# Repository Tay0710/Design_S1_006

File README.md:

# ELEC5550 Group Project (Team 0-06)

**Students Involved:**
- Aidan	Wheller
- Dorothy	Jong
- Emersyn Johnson
- Owen Spicer
- Samuel Dixon
- Taylah Karran

## 🚀 Project Summary

This project integrates hardware, firmware, and design elements to develop a fully functional autonomous 3D mapping drone system. This iteration of the design involves a drone capable of autonomously navigating the operation environment of Lv4 EECE, a LoRa-based kill switch which covers the entire operation environment, a mapping test rig used to manually collect data from 2 independent mapping systems, and a 3D mapping python pipeline which runs on the base station, used to convert raw mapping data from the test rig into 2 independent maps plus a combined map.

The next iteration of this design aims to combine the mapping test rig with the autonomous drone platform, creating a fully integrated autonomous 3D mapping drone system which follows the system architecture diagram below.

.png)

## 📁 Folder Structure

```
📁 Root Directory

├── 📂 3D Mapping
│   └── 3D mapping
│   └── optical_flow_method
│   └── optical_flow_method_data
│
├── 📂 CAD Design
│   └── 3D-printed Parts
│   └── Full_Model
│   └── LoRa Kill Switch
│
├── 📂 Drone Firmware
│   └── Flight Computer Firmware
│   └── Flight Controller Firmware
│
├── 📂 LoRa Drone Receiver Test Firmware
│   └── LORA_DRONE_RECEIVER
│
├── 📂 LoRa Kill Switch Firmware
│   └── LORA_TRANSMITTER_BUTTON
│
├── 📂 PCB Design
│   └── ESP32_BOARD_V2
│   └── STM32_BOARD_V3
│
├── 📂 Test Rig Firmware
│   └── Test Rig Data Collection
│   └── Test Rig FreeRTOS
│
└── 📂 Videos
```

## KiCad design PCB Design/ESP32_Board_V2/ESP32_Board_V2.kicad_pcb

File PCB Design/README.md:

# ELEC5550 Group Project (Team 0-06)

**Students Involved:**
- Aidan	Wheller
- Dorothy Jong
- Emersyn Johnson
- Owen Spicer
- Samuel Dixon
- Taylah Karran

## 📁 Project Overview - PCB Design

**Folder Summary:**

This folder contains all PCB schematics, design files, and related documentation required for manufacturing the printed circuit board (PCB) for the ESP32 flight computer and STM32 flight controller. It includes the necessary Gerber files, bill of materials (BOM), and design source files to ensure accurate production and assembly. All PCB projects can be viewed through KiCAD, which can be downloaded through this [link](https://www.kicad.org/download/).

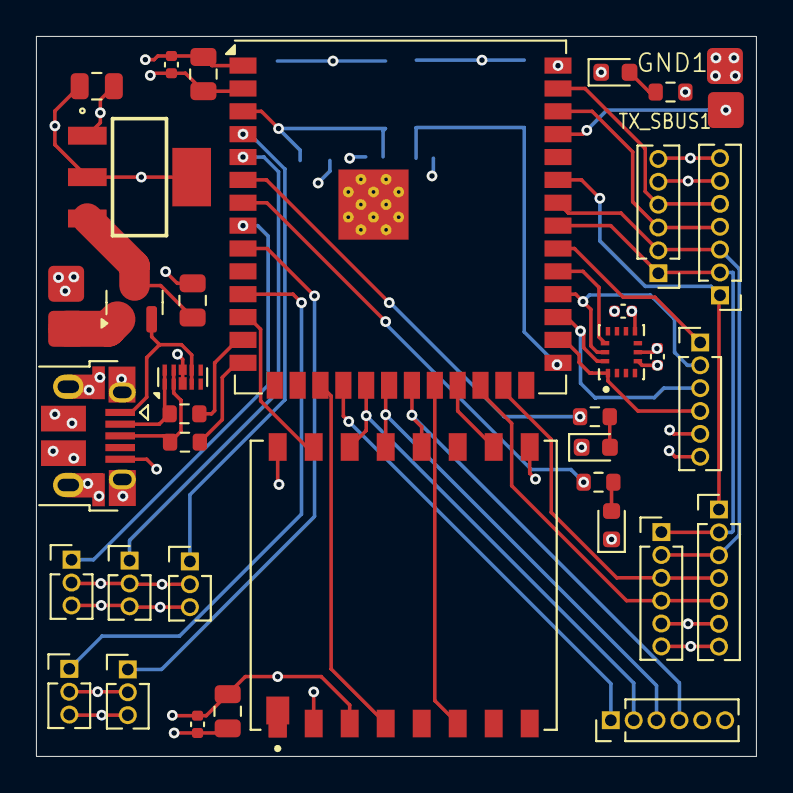
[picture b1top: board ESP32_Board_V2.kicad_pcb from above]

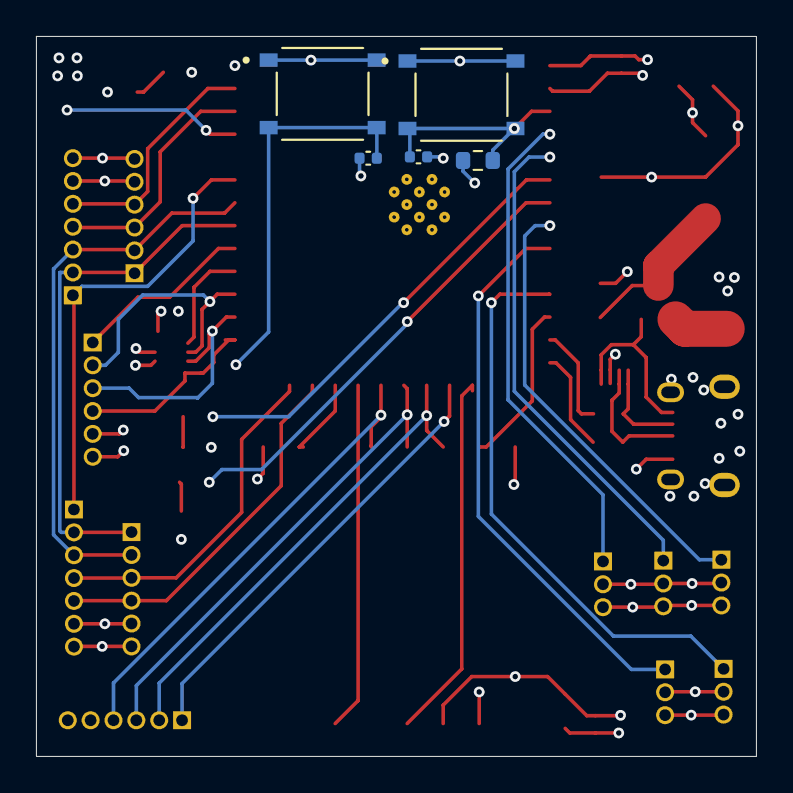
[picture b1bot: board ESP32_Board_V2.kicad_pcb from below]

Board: 4 copper layers, 40.0 x 40.0 mm, 42 parts (5 on the bottom side), 42 nets.

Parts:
C1, C15: 10u/10V; C_0805_2012Metric
C2: 100n/10V; C_0402_1005Metric
C9, C12, C13, C14, C23: 0.1u/10V; C_0402_1005Metric
C17, C19: 10u/16V; C_0805_2012Metric
D1, D4, D5: LED; LED_0603_1608Metric
D6: BAT54C; SOT-23
ESP3V3: NCP1117ST33T3G; SOT230P700X180-4N
GND1: GND; SolderPad_2mm
J6: USB_B_Micro; USB_Micro-B_Amphenol_10103594-0001LF_Horizontal
J7: US1; PinHeader_1x03_P1.27mm_Vertical
J8: US2; PinHeader_1x03_P1.27mm_Vertical
J9: US3; PinHeader_1x03_P1.27mm_Vertical
J10: US4; PinHeader_1x03_P1.27mm_Vertical
J11: US5; PinHeader_1x03_P1.27mm_Vertical
J12: TOF1; PinHeader_1x06_P1.27mm_Vertical
J13: TOF2; PinHeader_1x07_P1.27mm_Vertical
J14: TOF3; PinHeader_1x06_P1.27mm_Vertical
J15: TOF4; PinHeader_1x07_P1.27mm_Vertical
J16: SD Card; PinHeader_1x06_P1.27mm_Vertical
J17: Optical Flow; PinHeader_1x06_P1.27mm_Vertical
J20: BATTERYESP; 2_SolderPad_2mm
R1, R8, R9: 1k; R_0603_1608Metric
R10, R11: 22; R_0603_1608Metric
R12: 10k; R_0603_1608Metric
S1, S2: TS-1187A-B-A-B; SW_TS-1187A-B-A-B
TX_SBUS1: TX_SBUS; SolderPad_2mm
U1: ESP32-S3-WROOM-1; ESP32-S3-WROOM-1U
U2: RA-01H; XCVR_RA-01H
U5: D3V3XA4B10LP; Diodes_UDFN-10_1.0x2.5mm_P0.5mm
U7: ICM-45686; IC_ICM-45686

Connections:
/ESP32/3V3: C1.1, C2.1, C9.2, C14.1, C15.1, C17.1, C23.2, ESP3V3.2 (OUT), ESP3V3.4 (OUT), J7.2, J8.2, J9.2, J10.2, J11.2, J12.5, J13.6, J14.5, J15.6, J16.5, J17.5, R1.2, R12.1, U1.2 (3V3), U2.3 (3.3V), U7.5 (VDDIO), U7.8 (VDD)
/ESP32/5V_USB2: D6.2, J6.1 (VBUS), U5.4, U5.7 (NC)
/ESP32/AP_CS2: U1.31 (IO38), U7.12 (AP_CS)
/ESP32/AP_SCLK2: J17.2, U1.30 (IO37), U7.13 (AP_SCL/AP_SCLK)
/ESP32/AP_SDI2: J17.3, U1.29 (IO36), U7.14 (AP_SDA/AP_SDIO/AP_SDI)
/ESP32/AP_SDO2: J17.4, U1.28 (IO35), U7.1 (AP_SDO/AP_AD0)
/ESP32/BOOT: C13.1, S2.C, S2.D, U1.27 (IO0)
/ESP32/CLK1: J16.4, U1.21 (IO13), U2.12 (SCK)
/ESP32/CSLORA: U1.12 (IO8), U2.15 (NSS)
/ESP32/CSOF: J17.1, U1.32 (IO39)
/ESP32/CSSD: J16.1, U1.18 (IO10)
/ESP32/ENABLE: C12.1, R12.2, S1.C, S1.D, U1.3 (EN)
/ESP32/LED3: R8.2, U1.6 (IO6)
/ESP32/LED4: R9.2, U1.7 (IO7)
/ESP32/LORA_BUSY: U1.23 (IO21), U2.10 (BUSY)
/ESP32/LORA_DIO: U1.22 (IO14), U2.6 (DIO1)
/ESP32/LORA_RESET: U1.17 (IO9), U2.4 (RESET)
/ESP32/LPN: J13.1, J15.1, U1.35 (IO42)
/ESP32/MISO1: J16.3, U1.20 (IO12), U2.13 (MISO)
/ESP32/MOSI1: J16.2, U1.19 (IO11), U2.14 (MOSI)
/ESP32/PENA: J12.1, J13.2, J14.1, J15.2, U1.33 (IO40)
/ESP32/RESET: J12.2, J13.3, J14.2, J15.3, U1.34 (IO41)
/ESP32/SCL1: J12.4, J13.5, U1.24 (IO47)
/ESP32/SCL2: J14.4, J15.5, U1.39 (IO1)
/ESP32/SDA1: J12.3, J13.4, U1.25 (IO48)
/ESP32/SDA2: J14.3, J15.4, U1.38 (IO2)
/ESP32/TX0: TX_SBUS1.1, U1.37 (TXD0)
/ESP32/US1: J7.1, U1.11 (IO18)
/ESP32/US2: J8.1, U1.8 (IO15)
/ESP32/US3: J9.1, U1.9 (IO16)
/ESP32/US4: J10.1, U1.4 (IO4)
/ESP32/US5: J11.1, U1.5 (IO5)
/ESP32/USB_N: J6.2 (D-), R10.2, U5.1, U5.10 (NC)
/ESP32/USB_P: J6.3 (D+), R11.2, U5.2, U5.9 (NC)
GND: C1.2, C2.2, C9.1, C12.2, C13.2, C14.2, C15.2, C17.2, C19.2, C23.1, D1.1 (K), D4.1 (K), D5.1 (K), ESP3V3.1 (GND), GND1.1, J6.5 (GND), J6.6 (Shield), J7.3, J8.3, J9.3, J10.3, J11.3, J12.6, J13.7, J14.6, J15.7, J16.6, J17.6, J20.2, S1.A, S1.B, S2.A, S2.B, U1.1 (GND), U1.40 (GND), U1.41 (GND), U2.2 (GND), U2.9 (GND), U2.16 (GND), U5.3 (VSS), U5.8 (VSS), U7.6 (GND)
unnamed: D1.2 (A), R1.1
unnamed: D4.2 (A), R8.1
unnamed: D5.2 (A), R9.1
unnamed: C19.1, D6.3, ESP3V3.3 (IN)
unnamed: D6.1, J20.1
unnamed: R11.1, U1.14 (USB_D+)
unnamed: R10.1, U1.13 (USB_D-)

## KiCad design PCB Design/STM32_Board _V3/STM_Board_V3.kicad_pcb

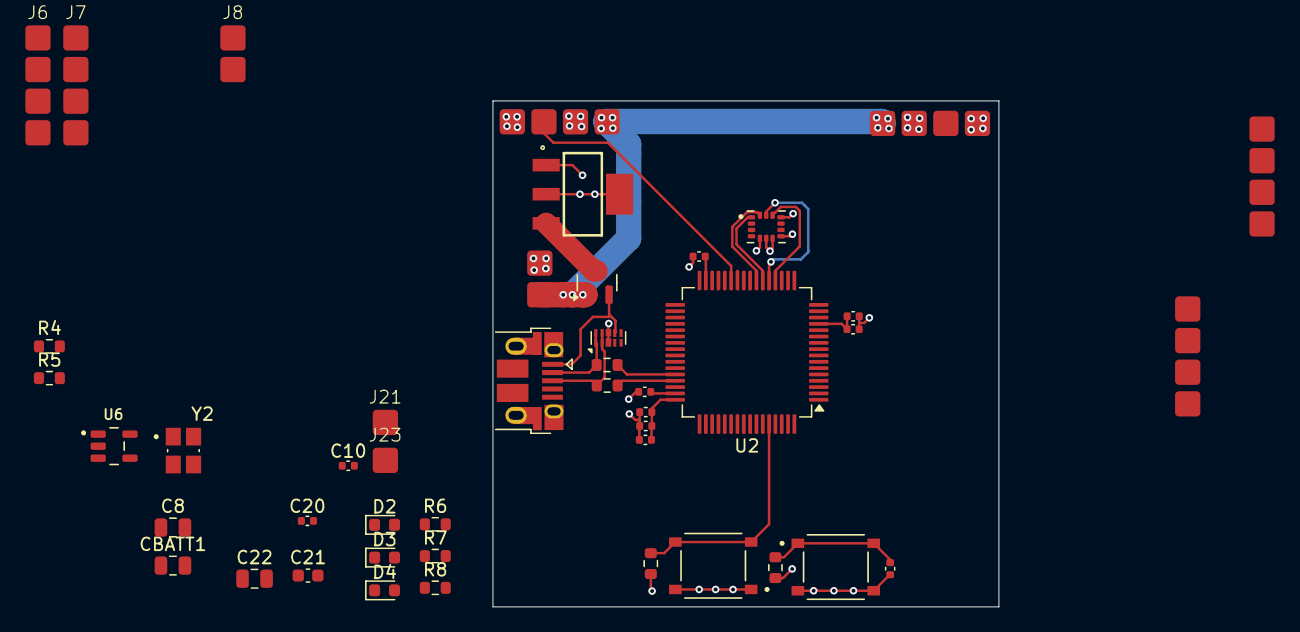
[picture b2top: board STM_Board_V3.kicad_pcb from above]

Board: 4 copper layers, 40.0 x 40.0 mm, 46 parts (0 on the bottom side), 39 nets.

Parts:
C1, C2, C3, C4, C5, C6, C7, C10, C20: C49062; C_0402_1005Metric
C8: C1713; C_0805_2012Metric
C9: 100n; C_0402_1005Metric
C21: C1531; C_0603_1608Metric
C22: C1710; C_0805_2012Metric
CBATT1: C1713; C_0805_2012Metric
D1: C2135; SOT-23
D2, D4: C2286; LED_0603_1608Metric
D3: C2290; LED_0603_1608Metric
J1: C136001; USB_Micro-B_Amphenol_10103594-0001LF_Horizontal
J2: S1; 4_SolderPad_2mm
J3: S2; 4_SolderPad_2mm
J4: S3; 4_SolderPad_2mm
J5: S4; 4_SolderPad_2mm
J6: ST-LINK; 4_SolderPad_2mm
J7: UART-FLASH; 4_SolderPad_2mm
J8: SBUS; 2_SolderPad_2mm
J18: BATTERYSTM; 2_SolderPad_2mm
J21: STM32GROUND; SolderPad_2mm
J23: SBUS_IN; SolderPad_2mm
R1, R4, R5: C15401; R_0603_1608Metric
R2, R3: C1203; R_0603_1608Metric
R6, R7, R8: C14676; R_0603_1608Metric
R9: 10k; R_0603_1608Metric
S1, S2: C318884; SW_TS-1187A-B-A-B
STM3V3: C26537; SOT230P700X180-4N
U1: D3V3XA4B10LP; Diodes_UDFN-10_1.0x2.5mm_P0.5mm
U2: C15742; LQFP-64_10x10mm_P0.5mm
U4: C1850418; PQFN50P300X250X97-14N
U6: C7827; SOT95P280X145-5N
Y2: C5140594; XTAL_ABM8AIG-8.000MHZ-1Z-T

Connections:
/IMU1/3V3: C1.1, C2.1, C3.1, C4.1, C5.1, C8.1, C10.2, C20.2, C21.2, C22.1, J6.3, J7.3, R8.2, R9.2, S2.A, S2.B, STM3V3.2 (OUT), STM3V3.4 (OUT), U2.1 (VBAT), U2.13 (VDDA), U2.19 (VDD), U2.32 (VDD), U2.48 (VDD), U2.64 (VDD), U4.5 (VDDIO), U4.8 (VDD), U6.5
/LEDs/LED1: R6.2, U2.56 (PB4)
/LEDs/LED2: R7.2, U2.57 (PB5)
/STM32/5V_USB1: D1.2, J1.1 (VBUS), R5.1, U1.4, U1.7 (NC)
/STM32/AP_CS: U2.20 (PA4), U4.12 (AP_CS)
/STM32/AP_SCLK: U2.21 (PA5), U4.13 (AP_SCL/AP_SCLK)
/STM32/AP_SDI: U2.23 (PA7), U4.14 (AP_SDA/AP_SDIO/AP_SDI)
/STM32/AP_SDO: U2.22 (PA6), U4.1 (AP_SDO/AP_AD0)
/STM32/BATT: D1.1, J2.1, J3.1, J4.1, J5.1, J18.1
/STM32/BOOT: R1.1, S2.C, S2.D, U2.60 (BOOT0)
/STM32/INT1: U2.24 (PC4), U4.4 (INT1/INT)
/STM32/INT2: U2.28 (PB2), U4.9 (INT2/FSYNC/CLKIN)
/STM32/RESET: C9.2, R9.1, S1.A, S1.B, U2.7 (NRST)
/STM32/RX_4: U2.15 (PA1), U6.4
/STM32/RX_ESP32_IN: J23.1, U6.2
/STM32/RX_SBUS: J8.1, U2.54 (PD2)
/STM32/S1: J2.3, U2.17 (PA3)
/STM32/S2: J3.3, U2.26 (PB0)
/STM32/S3: J4.3, U2.27 (PB1)
/STM32/S4: J5.3, U2.16 (PA2)
/STM32/SWCLK: J6.2, U2.49 (PA14)
/STM32/SWDIO: J6.1, U2.46 (PA13)
/STM32/TX_SBUS: J8.2, U2.53 (PC12)
/STM32/USART1_RX: J7.1, U2.43 (PA10)
/STM32/USART1_TX: J7.2, U2.42 (PA9)
/STM32/USB_N: J1.2 (D-), R3.2, U1.1, U1.10 (NC)
/STM32/USB_P: J1.3 (D+), R2.2, U1.2, U1.9 (NC)
GND: C1.2, C2.2, C3.2, C4.2, C5.2, C6.2, C7.2, C8.2, C9.1, C10.1, C20.1, C21.1, C22.2, CBATT1.2, D2.1 (K), D3.1 (K), D4.1 (K), J1.5 (GND), J1.6 (Shield), J2.2, J2.4, J3.2, J3.4, J4.2, J4.4, J5.2, J5.4, J6.4, J7.4, J18.2, J21.1, R1.2, R4.2, S1.C, S1.D, STM3V3.1 (GND), U1.3 (VSS), U1.8 (VSS), U2.12 (VSSA), U2.18 (VSS), U2.63 (VSS), U4.6 (GND), U4.7 (RESV_7), U4.11 (RESV_11), U6.1, U6.3, Y2.2 (GND), Y2.4 (GND__1)
unnamed: D2.2 (A), R6.1
unnamed: D3.2 (A), R7.1
unnamed: D4.2 (A), R8.1
unnamed: CBATT1.1, D1.3, STM3V3.3 (IN)
unnamed: R3.1, U2.44 (PA11)
unnamed: R2.1, U2.45 (PA12)
unnamed: R4.1, R5.2, U2.25 (PC5)
unnamed: U2.5 (PH0), Y2.3
unnamed: U2.6 (PH1), Y2.1
unnamed: C7.1, U2.31 (VCAP_1)
unnamed: C6.1, U2.47 (VCAP_2)

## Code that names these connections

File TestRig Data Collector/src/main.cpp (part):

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#include <Bitcraze_PMW3901.h>

// Optical flow SPI pins (pins for Owen's ESP32)
#define MOSI1 11 // OF, VSPI
#define CLK1 12
#define MISO1 13
#define CS1 10

#define AP_SDI2 37 // IMU / ICM - PSRAM
#define AP_CLK2 36 // SDO = MISO; SDI = MOSI
#define AP_SDO2 38
#define AP_CS2 35

#define SDCLK 47 // SD Card, HSPI
#define SDMISO 48
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#define SDA2 6
#define SCL2 7
// ToF inputs. 
#define PENA 41 // Power enable
#define RESET 40
#define LPN 42

#define US1 14
#define US2 15
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
// Address Reset sequence for ToFL7 sensors.
// Activating PWR_EN (Make High). 
  pinMode(PENA, OUTPUT);
  digitalWrite(PENA, HIGH); 
  delay(100);   
// Activating I2C Reset pin to reset the addresses (Pulse High). 
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  delay(100);   
  digitalWrite(PENA, HIGH); // Make High again.
  delay(100);  
  // Configure LPn pins
  pinMode(LPN, OUTPUT);
  // Set Sensor 1 LPn low (Deactivate I2C communication). 
  digitalWrite(LPN, LOW); // One LPn should be set HIGH permanently
  delay(100); 

  // I2C Bus split: S1 + R on I2C1; S2 + F on I2C2
  // Have to change the address of the ToFs with no LPN pin attached.
  // Make R & F the changed Address sensors. 


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
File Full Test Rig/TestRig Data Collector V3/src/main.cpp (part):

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#define VSPI_MOSI 36 // OF and IMU, VSPI
#define VSPI_CLK 37
#define VSPI_MISO 35
#define CSOF 39
#define CSIMU 38

#define HSPI_CLK 13 // SD Card, HSPI
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#define SCL1 47  
#define SDA2 2
#define SCL2 4
#define PENA 40 // Power enable
#define RESET 41 // I2C reset
#define LPN 42

#define USD 15 // Downwards-mounted ultrasonic PW pin
// #define USU 4 // Upwards-mounted ultrasonic PW pin
#define USL 18 // Left-mounted ultrasonic PW pin
#define USR 5 // Right-mounted ultrasonic PW pin
#define LED1 6 // PCB LED

#define BOOT_PIN 0

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}

void setup() {
  pinMode(LED1, OUTPUT);
  delay(100);
  digitalWrite(LED1, HIGH);

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  // Initialise 4 ToF sensors
  // Address reset sequence for ToFL7 sensors.
  // Activating PWR_EN (Make High). 
  pinMode(PENA, OUTPUT);
  delay(200); 
  digitalWrite(PENA, HIGH); 
  delay(200);   
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  delay(200);   
  digitalWrite(PENA, HIGH); // Make high again
  delay(200);  
  // Configure LPn pins
  pinMode(LPN, OUTPUT);
  delay(200);
  // Set sensor 1 LPn low (Deactivate I2C communication) 
  digitalWrite(LPN, LOW); // One LPn should be set HIGH permanently
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  Serial.println("Clock Has been Set for I2Cs");

  // I2C bus split: L + U on I2C_bus2; R + D on I2C_bus1
  // Have to change the address of the ToFs with no LPN pin attached.
  // U + D are the sensors that have their address changed

  // Change sensor address to 0x30 after calling begin()
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
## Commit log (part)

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2025-09-18 Added detail to README
2025-09-18 Updated orientation
2025-09-18 Fixed orientation
2025-09-18 Added READMEs
2025-09-18 Created for mapping base.
2025-09-18 added figures for Lshaped data
2025-09-18 Created to transition the test code to a real data point from the ToF.
2025-09-18 Position pipeline ran to update data files.
2025-09-18 Added README
2025-09-18 Changed frequency of OF
2025-09-18 fixed OF y velocity direction
2025-09-18 add figure
2025-09-18 update data
2025-09-18 updated data s2
2025-09-18 Created to transition to all data sets from one sample tof data set in a previous script. Working well.
2025-09-18 added data times
2025-09-18 tuned scale factor for tof and fixed imu truncation
2025-09-19 Updated to include overarching documentation.
2025-09-19 Updated to include mesh.
2025-09-19 Updated to remove the outliers less than 0.2m from the drone. Mesh is not right so it has been commented out.
2025-09-19 Updated documentation.
2025-09-19 Update spacing.
2025-09-19 Created README.
2025-09-19 added more comparisons
2025-09-19 Changed board and made new project
2025-09-19 Added reading for the SQUAL and SHUTTER registers
2025-09-19 Archived old code
2025-09-19 Wrote code to read ultrasonic using interrupts
2025-09-19 updated x4 with differentiated acceleration
2025-09-19 Updated files
2025-09-19 Updated pins
2025-09-19 Changed buffer sizes and variable names
2025-09-19 Changed dps
2025-09-20 sync
2025-09-20 notes
2025-09-20 two US interrupts, w timing
2025-09-20 Added extra time variables
2025-09-20 Changed frequency and comments
2025-09-20 Moved auxiliary functions
2025-09-20 Changed ToF to separate CSVs and renamed pins
2025-09-20 Changed ultrasonic functions such that they now use interupts
2025-09-20 Changed SPI bus initialisation
2025-09-20 Standardised initialisation structure
2025-09-20 Changed ToF sensor names
2025-09-20 Added files for each ToF
2025-09-20 Added extra files to closing process
2025-09-20 Fixed i2c issue for sensor U
2025-09-21 updating
2025-09-21 Fixed i2c bus issues
2025-09-21 Removed alternate code
2025-09-21 Merged ToF data into one file such that the max number of files open is not exceeded
2025-09-21 Chaning the order of logic for ToF data collection.
2025-09-21 Removed unnecessary int
2025-09-21 Changed ToF to common timestamp
2025-09-21 Changed ultrasonic pin, fixing ultrasonic data collection
2025-09-21 Added frequency specification to increase polling speed
2025-09-21 Moved ToF timer check out of individual ToF function
2025-09-21 Removed delay printing
2025-09-21 Swapped pins of sensors L and R
2025-09-22 Fixed ToF indexing issue
2025-09-22 Minor formatting
2025-09-22 New sample with full test rig
2025-09-22 Added two new samples
2025-09-22 Added samples
2025-09-22 New sample
2025-09-22 Added sample 7
2025-09-22 Updated to match the new tof file format with type column.
2025-09-22 From pipeline run.
2025-09-22 Updated to include functions for the up and down tof.
2025-09-22 Saved images for tof mapping progress.
2025-09-22 Created video for full map of 1_rectangle.
2025-09-22 Updated to include the 8x8 tofs on the left and right.
2025-09-22 Updated to run various data sets.
2025-09-23 Updated times on README
2025-09-23 work in progress: updating z positioning
2025-09-23 include z position in csv
2025-09-23 added 7_lyco_lab data set
2025-09-23 rtos code
2025-09-23 1_L_cards sample added
2025-09-23 2 samples added
2025-09-23 updated screen and button
2025-09-23 Addition of MUTEX for SD card write
2025-09-23 Fixing Debounce Button
2025-09-23 added acceleration in world frame
2025-09-23 added new imu experiments
2025-09-24 Updated for new sample.
2025-09-24 Updated to incorporate the rotation matrix in the ToF distance calculation.
2025-09-24 Update comments.
2025-09-24 Fixing ToF racing condition and Stack smashing protect failure (increase Char size)
2025-09-24 correcting tof task core
2025-09-24 Added read of z_pos_body array
2025-09-24 Currently Crashes out after 53seconds of CSV recording.
2025-09-24 Generalised rotate_to_world function
2025-09-24 Added function to rotate z position to world
2025-09-24 Added function to generate rotated z position then added
2025-09-24 Changed code to add the z position witin the function. Renamed function to add_z_position
2025-09-24 Removed call of rotate world function in the add_z_position code
2025-09-25 update button to match pcb
2025-09-26 Added threshold to z_position_calc function
2025-09-26 Added pillar 2 sample
2025-09-26 Moved folders and added wrapping paper
2025-09-26 update things
2025-09-26 Addition of Ultrasonic Detection
2025-09-26 Implemented Hover code with Ultrasonic
2025-09-26 Implementing nonblocking throttle delays
2025-09-27 Fixed sensor axis orientation, fov and negated y-axis ToF angles
2025-09-27 Removed the need for the cell_angles arrays
2025-09-27 add changes to test file
2025-09-27 update requirements
2025-09-27 added new version with new maths
2025-09-27 added a statistical outlier filter
2025-09-29 adding pid lib
    adding pid lib
2025-09-29 adding pid code.
2025-09-29 udpatessss
2025-09-29 PID tuning
2025-09-29 added colours for each sensor
2025-10-01 Added data collector V3 code
2025-10-01 adding prints + create sdcard module test file
2025-10-01 included speed write test
2025-10-01 I agree it does not work.
2025-10-01 Added offsets to the point cloud generation
2025-10-02 Added lv4 sticker samples
2025-10-02 add debounce to dpad, add higher throttle value to arm sequence
2025-10-02 added new folder
2025-10-02 fixed some pid stuff
2025-10-03 changed throttle values
2025-10-03 Update pipeline and optical flow folder to remove references to stages 7/8.
2025-10-04 added sync words for private LoRa networks
2025-10-05 drone hover testing
2025-10-05 returns a point distance.
2025-10-05 pitch adjustments testing
2025-10-06 pitch code improvement
2025-10-06 not sure
2025-10-06 Update current tof map name.
2025-10-06 Updated to remove the main call of deleted stages 7/8.
2025-10-06 Created ultrasonic map based off of the tof code. Included capacity to crop the ultrasonic data.
2025-10-06 Updated to link to the mapping pipeline.
2025-10-06 Updated to remove the crop code as this functionality has been moved to the mapping pipeline file.
2025-10-06 Updated to remove double-up of numpy import.
2025-10-06 Moved file to the archive folder.
2025-10-06 Created file through the mapping pipeline.
2025-10-06 Updated to include new mapping pipeline.
2025-10-06 Moved unnecessary mapping files to archive.
2025-10-06 Updated to include how to run the position and mapping pipelines.
2025-10-06 Updated to remove the oython 11 version note.
2025-10-06 Updated to include to save the tof and us point clouds and combine them.
2025-10-06 Added final flight controller firmware
    Upload using STMCubeProgrammer
2025-10-07 addaition of front US code. and arm sequence changes.
2025-10-07 addition of ToF
    increasing pitch due to extra weight, as well as throttle. Testing YAW with TOF works nicely.
2025-10-07 notes added
2025-10-08 Reorganise previous method filesl
2025-10-08 Updated to include corner extrapolation.
2025-10-08 Created a new version for the introduction of wall extrapolation.
2025-10-08 Updated to include additional extrapolation.
2025-10-09 Removed loop activity pin
2025-10-09 Pins changed for testing
2025-10-09 Changed to S3 board
2025-10-10 logic fixes with drone turning Left
2025-10-10 syntax fixes.
2025-10-10 fixed settings for single wire antenna
2025-10-10 Changed pins
2025-10-10 Changed board to S3
2025-10-10 Added custom i2c pins
2025-10-10 Changed to ESP32 S3
2025-10-10 Changed pin numbers to match PCB
2025-10-10 Updated pins to match new PCB
2025-10-10 Update bins and bus type
2025-10-10 New project added for simple IMU data collection
2025-10-10 Renamed project
2025-10-10 Made new code for sampling two ToFs on one I2C bus
2025-10-14 Updates file names.
2025-10-14 Added fake ultrasonic data to lyco sample
2025-10-15 Update to call new extrapolated ultrasonic code through the pipeline.
2025-10-15 Updated the filepath.
2025-10-15 Updated to include fusion attempt.
2025-10-15 Updated to include combination map.
2025-10-15 Created to create individual tof and ultrasonic maps, as well as a combination map with filtering.
2025-10-16 udpate
2025-10-16 Roll works
2025-10-18 Changed US pins
2025-10-20 Updated to include new colours.
2025-10-21 Moving LED blink
2025-10-22 Added test rig V4
2025-10-22 Updated the requirements file.
2025-10-22 Updated to include all maps.
2025-10-22 Created to display various forms of filtering in the XY axes on the fused map.
2025-10-22 new samples
2025-10-22 Comparison of map filtering images.
2025-10-22 Updated to remove extrapolated ultrasonic data.
2025-10-22 fixed lora for drone pcb
2025-10-22 New files based on updated data.
2025-10-22 Updated for new data.
2025-10-22 update lora take off code
2025-10-22 Corrected pins
2025-10-22 Minor changes
2025-10-22 It works lol
    Has pitch braking and yaw corner turning.
2025-10-22 Fixed orientations
2025-10-23 Adding new sample data
2025-10-23 Improved orientation conversion
2025-10-23 Improved orientation
2025-10-23 Created to remove the downward ultrasonic.
2025-10-23 add sensor copy 2 for tof testing on drone
2025-10-23 organised file structure
2025-10-23 Updated for new filepath.
2025-10-23 Changed data time
2025-10-23 Updated filepaths.
2025-10-23 yaw adjustments.
2025-10-23 completed flight controller README
2025-10-23 Moved CSVs
2025-10-23 moved over code from ardunino
2025-10-23 Added velocity filter
2025-10-23 Updated the unit conversion.
2025-10-23 Fix merge issues.
2025-10-23 good code
2025-10-23 updated pitching due to ultrasonic sensor error
2025-10-23 updated pins for left ultrasonic sensor
2025-10-24 Fixed rotation issue
2025-10-24 Reverted unnecessary changes back to prev
2025-10-24 Fixed ultrasonic again
2025-10-24 throttle changes
2025-10-24 New ultrasonic code
2025-10-24 added US RX init
2025-10-24 Updated to test 3 MB1030s
2025-10-24 LEFT WALL ULTRA added
2025-10-24 minor changes to height and US L int
2025-10-24 roll changes
2025-10-24 updated sensor mb1030
2025-10-24 Adding new RTOS code
2025-10-24 Formatting and manual calibration
2025-10-24 Changed to ultrasonic UART daisy chain
2025-10-24 small1
2025-10-24 unfinshed battery compensation.
2025-10-24 test this 1 more time. (battery compensation added).
2025-10-25 nothing 1.0
2025-10-25 end of 25_10_2025
2025-10-25 notes.
2025-10-26 Made the velocity correction configurable to apply to smaller percentages of the sample
2025-10-26 turning - not working atm.
2025-10-26 Added third Sample
2025-10-26 work's best code (even roll & higher lift off throttle)
2025-10-26 very good straight down the middle.
2025-10-26 Added swivel sample
2025-10-27 braking adjustments.
2025-10-27 braking minor changes to improve.
2025-10-27 added soft landing
2025-10-27 Added test rig code
2025-10-27 updated lora test code to have less print statements
2025-10-27 update lora drone receiver test firmware
2025-10-27 added PCB files
2025-10-27 added README.md
2025-10-27 Create Full Model
2025-10-27 Delete CAD Design/Full Model
    oops
2025-10-27 Create Full_Model_Components
2025-10-27 Add files via upload
    Full Model
2025-10-27 Create Video Description
2025-10-27 updated Videos folder
2025-10-27 Updated READMEs
2025-10-27 Fixed header file error
2025-10-27 Fixed README name
2025-10-27 Updated file to finalise documentation.
2025-10-27 Updated files to finalise documentation.
2025-10-28 Ran new data.
2025-10-28 added STL files
2025-10-28 added sensor mount STL files
2025-10-28 Updated to remove the duplicate ToF map.
2025-10-28 Remove unnecessary detail. Add in the distance constraint.
2025-10-28 Reorganised the archive mapping folder.
2025-10-28 Update mapping and position READMEs.
2025-10-28 made new project
2025-10-28 Updated file to finalise documentation and include the addition of corners using the synthesised "Down" data points.
2025-10-28 Updated to include extrapolation for the ultrasonic data and the fused data.
2025-10-28 Updated to remove the polygon border.
2025-10-28 Updated file to finalise the documentation.
2025-10-28 Updated to include the demonstration data filepath.
2025-10-28 update folder structure
